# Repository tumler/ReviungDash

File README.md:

# REVIUNGDASH

## REVIUNGDASH47

The REVIUNGDASH47 is 47/8 key column staggered keyboard. Inspired by the Reviung41
(& ERGODASH) hence the name!

[REVIUNGDASH47](reviungdash47/)

## REVIUNGDASH52

The REVIUNGDASH52 is a 52 key column staggered keyboard. Based on the
REVIUNGDASH47 but with a larger thumb cluster.

[REVIUNGDASH52](reviungdash52/)

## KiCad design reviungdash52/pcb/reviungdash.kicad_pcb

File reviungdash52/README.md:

# REVIUNGDASH52

The REVIUNGDASH52 is a 52 key column staggered keyboard. Based on the
REVIUNGDASH47 but with a larger thumb cluster.

[REVIUNGDASH52](reviungdash52/)
The REVIUNGDASH47 is 47/8 key column staggered keyboard. Inspired by the Reviung41
(& ERGODASH) hence the name!

Differences between the REVIUNGDASH47:

* Addition of a thumb cluster - inspired by the Ergodash cluster
    * 2 Extra thumb keys each side
* Left / Right sides further apart to accomodate thumb cluster, while remaining
as close as possible to remain small yet comfortable
* Every layer designed as PCBs (could easily be swapped out for acrylic / metal layers)

## Parts list  

* Top plate (PCB / Metal) 1.6mm --- 1
* Inner w/ MCU Cutout 1.2mm --- 4
* PCB 1.6mm --- 1
* Inner without MCU Cutout 1.6mm --- 1
* Bottom Plate 1.6mm --- 1

* MCU (ProMicro or RP2040 that has the same dimensions as a ProMicro)

* Using Magnets as feet / standoffs:
* M2 Screw 5mm --- 22 pieces
* M2 Screw 6mm --- 4 pieces (to attach the magnets)
* Through-hole M3 Magnets --- 4 pieces (+ as many as you need for the height you want for the standoffs)

* No standoffs (or using another system):
* M2 Screw 5mm --- 26 pieces

* Rubber Feet --- 6 pieces (might require different sizes on the 2 internal legs - see photos)

* Diode [1N4148 SMD] --- 52 pieces  
* MX compatible key switch --- 52 pieces  

* Keycaps
* USB-C Cable --- 1

## Firmware

Based on QMK

* Works with VIAL UI (layout provided)
* QMK Config (layout provided - has not been tested)

[Vial-QMK Firmware](https://github.com/tumler/vial-qmk/tree/Add_ReviungDash_Keyboards)

## Build Guide

* See Reviung41 guide

[Build guide](https://reviung.com/build-guide/391/)

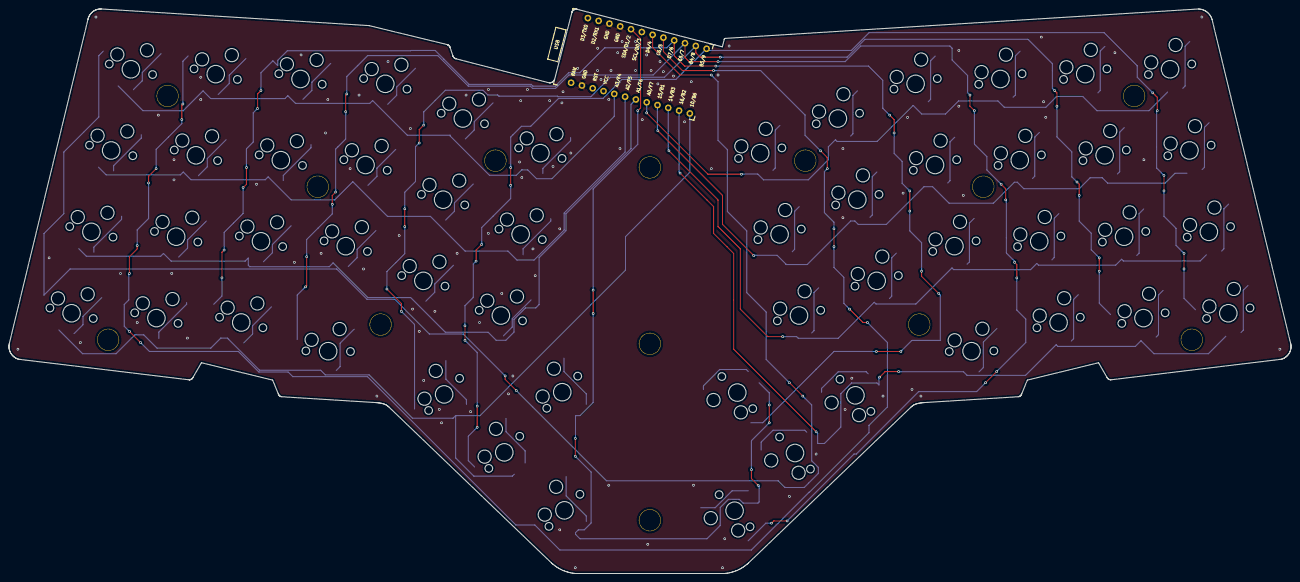
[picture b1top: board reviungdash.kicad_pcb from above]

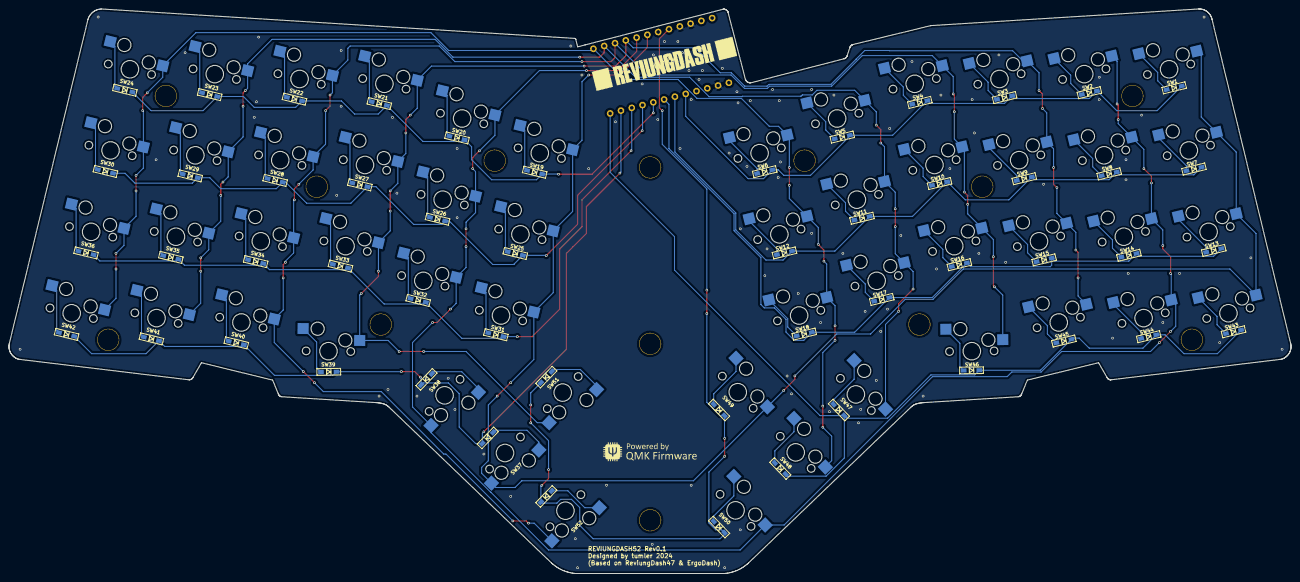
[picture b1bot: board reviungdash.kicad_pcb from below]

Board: 2 copper layers, 292.1 x 128.6 mm, 118 parts (52 on the bottom side), 68 nets.

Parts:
D1, D2, D3, D4, D5, D6, D7, D8, D9, D10, D11, D12, D13, D14, D15, D16, D17, D18, D19, D20, D21, D22, D23, D24, D25, D26, D27, D28, D29, D30, D31, D32, D33, D34, D35, D36, D37, D38, D39, D40, D41, D42, D43, D44, D45, D46, D47, D48, D49, D50, D51, D52: 1N4148W; D3_SMD_1side
H1: H1; MountingHoleLarge
H2: H2; MountingHoleLarge
H3: H3; MountingHoleLarge
H4: H4; MountingHoleLarge
H5: H5; MountingHoleLarge
H6, H15: H6; MountingHoleLarge
H7: H7; MountingHoleLarge
H8: H8; MountingHoleLarge
H9: H9; MountingHoleLarge
H10: H10; MountingHoleLarge
H11: H11; MountingHoleLarge
H16: H16; MountingHoleLarge
SW1, SW2, SW3, SW4, SW5, SW6, SW7, SW8, SW9, SW10, SW11, SW12, SW13, SW14, SW15, SW16, SW17, SW18, SW19, SW20, SW21, SW22, SW23, SW24, SW25, SW26, SW27, SW28, SW29, SW30, SW31, SW32, SW33, SW34, SW35, SW36, SW37, SW38, SW39, SW40, SW41, SW42, SW43, SW44, SW45, SW46, SW47, SW48, SW49, SW50, SW51, SW52: SW_PUSH; MXOnly-1U-Hotswap
U1: ProMicro

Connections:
GND: U1.3 (GND), U1.4 (GND), U1.23 (GND)
unnamed: D1.2 (A), SW1.2
unnamed: D2.2 (A), SW2.2
unnamed: D3.2 (A), SW3.2
unnamed: D4.2 (A), SW4.2
unnamed: D5.2 (A), SW5.2
unnamed: D6.2 (A), SW6.2
unnamed: D7.2 (A), SW7.2
unnamed: D8.2 (A), SW8.2
unnamed: D9.2 (A), SW9.2
unnamed: D10.2 (A), SW10.2
unnamed: D11.2 (A), SW11.2
unnamed: D12.2 (A), SW12.2
unnamed: D13.2 (A), SW13.2
unnamed: D14.2 (A), SW14.2
unnamed: D15.2 (A), SW15.2
unnamed: D16.2 (A), SW16.2
unnamed: D17.2 (A), SW17.2
unnamed: D18.2 (A), SW18.2
unnamed: D19.2 (A), SW19.2
unnamed: D20.2 (A), SW20.2
unnamed: D21.2 (A), SW21.2
unnamed: D22.2 (A), SW22.2
unnamed: D23.2 (A), SW23.2
unnamed: D24.2 (A), SW24.2
unnamed: D25.2 (A), SW25.2
unnamed: D26.2 (A), SW26.2
unnamed: D27.2 (A), SW27.2
unnamed: D28.2 (A), SW28.2
unnamed: D29.2 (A), SW29.2
unnamed: D30.2 (A), SW30.2
unnamed: D31.2 (A), SW31.2
unnamed: D32.2 (A), SW32.2
unnamed: D33.2 (A), SW33.2
unnamed: D34.2 (A), SW34.2
unnamed: D35.2 (A), SW35.2
unnamed: D36.2 (A), SW36.2
unnamed: D37.2 (A), SW37.2
unnamed: D38.2 (A), SW38.2
unnamed: D39.2 (A), SW39.2
unnamed: D40.2 (A), SW40.2
unnamed: D41.2 (A), SW41.2
unnamed: D42.2 (A), SW42.2
unnamed: D43.2 (A), SW43.2
unnamed: D44.2 (A), SW44.2
unnamed: D45.2 (A), SW45.2
unnamed: D46.2 (A), SW46.2
unnamed: D47.2 (A), SW47.2
unnamed: D48.2 (A), SW48.2
unnamed: D49.2 (A), SW49.2
unnamed: D50.2 (A), SW50.2
unnamed: D51.2 (A), SW51.2
unnamed: D52.2 (A), SW52.2
col0: SW1.1, SW7.1, SW13.1, SW19.1, SW25.1, SW31.1, SW37.1, SW43.1, SW49.1, U1.7 (4/D4)
col1: SW2.1, SW8.1, SW14.1, SW20.1, SW26.1, SW32.1, SW38.1, SW44.1, SW50.1, U1.8 (5/C6)
col2: SW3.1, SW9.1, SW15.1, SW21.1, SW27.1, SW33.1, SW39.1, SW45.1, SW51.1, U1.9 (6/D7)
col3: SW4.1, SW10.1, SW16.1, SW22.1, SW28.1, SW34.1, SW40.1, SW46.1, SW52.1, U1.10 (7/E6)
col4: SW5.1, SW11.1, SW17.1, SW23.1, SW29.1, SW35.1, SW41.1, SW47.1, U1.11 (8/B4)
col5: SW6.1, SW12.1, SW18.1, SW24.1, SW30.1, SW36.1, SW42.1, SW48.1, U1.12 (9/B5)
row0: D1.1 (K), D2.1 (K), D3.1 (K), D4.1 (K), D5.1 (K), D6.1 (K), U1.20 (F4/A3)
row1: D7.1 (K), D8.1 (K), D9.1 (K), D10.1 (K), D11.1 (K), D12.1 (K), U1.19 (F5/A2)
row2: D13.1 (K), D14.1 (K), D15.1 (K), D16.1 (K), D17.1 (K), D18.1 (K), U1.18 (F6/A1)
row3: D19.1 (K), D20.1 (K), D21.1 (K), D22.1 (K), D23.1 (K), D24.1 (K), U1.17 (F7/A0)
row4: D25.1 (K), D26.1 (K), D27.1 (K), D28.1 (K), D29.1 (K), D30.1 (K), U1.16 (B1/15)
row5: D31.1 (K), D32.1 (K), D33.1 (K), D34.1 (K), D35.1 (K), D36.1 (K), U1.15 (B3/14)
row6: D37.1 (K), D38.1 (K), D39.1 (K), D40.1 (K), D41.1 (K), D42.1 (K), U1.14 (B2/16)
row7: D43.1 (K), D44.1 (K), D45.1 (K), D46.1 (K), D47.1 (K), D48.1 (K), U1.13 (B6/10)
row8: D49.1 (K), D50.1 (K), D51.1 (K), D52.1 (K), U1.5 (2/D1/SDA)

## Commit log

2023-02-19 Add vial-qmk firmware link
2024-05-19 Add ReviungDash52
2024-05-19 Add Photos
